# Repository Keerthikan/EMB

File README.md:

# EMB
Github for Embedded course

Lektion01: BlinkyLED

1. Assignment: FSM 
2. Assignment: Sliding thing.. Color detector... yeah you know!..

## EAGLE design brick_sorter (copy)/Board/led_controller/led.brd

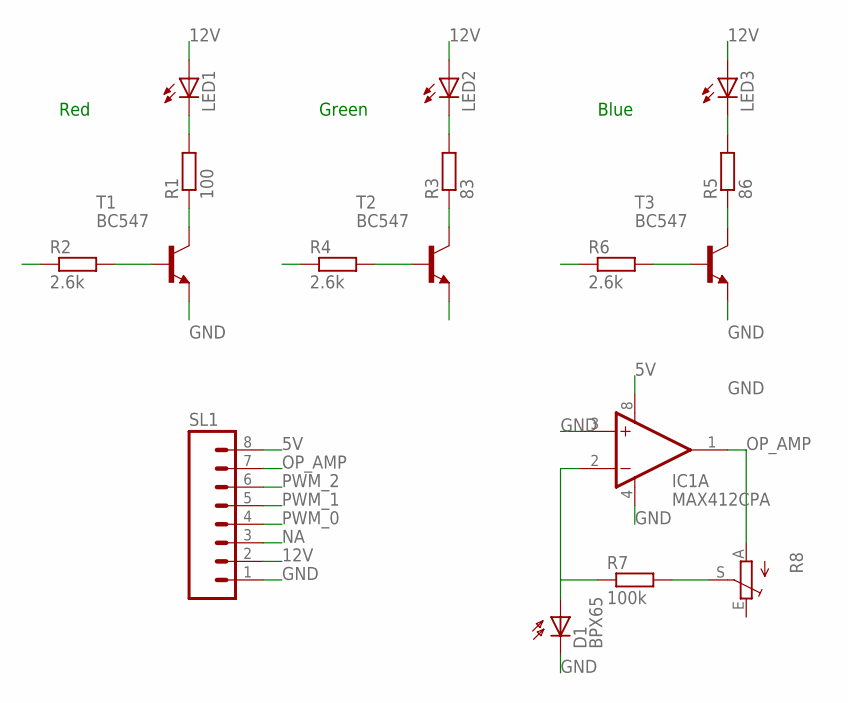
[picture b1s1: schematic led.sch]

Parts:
D1: BPX65
IC1: MAX412CPA; DIL08
LED1, LED2, LED3: LED_ELD260; LED_LD260
R1: 100; 0204/7
R2, R4, R6: 2.6k; 0204/7
R3: 83; 0204/7
R5: 86; 0204/7
R7: 100k; 0204/7
R8: TRIM_EU-B90P; SP19L
SL1: M08; 08P
T1, T2, T3: BC547; TO92

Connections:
5V: IC1.8 (V+), SL1.8
12V: LED1.A, LED2.A, LED3.A, SL1.2
GND: D1.K (C), IC1.3 (+IN), IC1.4 (V-), SL1.1, T1.1 (E), T2.1 (E), T3.1 (E)
unnamed: R4.2, T2.2 (B)
unnamed: LED1.K (C), R1.2
unnamed: R2.2, T1.2 (B)
unnamed: R1.1, T1.3 (C)
unnamed: LED2.K (C), R3.2
unnamed: R3.1, T2.3 (C)
unnamed: R6.2, T3.2 (B)
unnamed: LED3.K (C), R5.2
unnamed: R5.1, T3.3 (C)
unnamed: D1.A, IC1.2 (-IN), R7.1
unnamed: R7.2, R8.S
NA: SL1.3
OP_AMP: IC1.1 (OUT), R8.A, SL1.7
PWM_0: R2.1, SL1.4
PWM_1: R4.1, SL1.5
PWM_2: R6.1, SL1.6

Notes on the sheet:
Red
Green
Blue

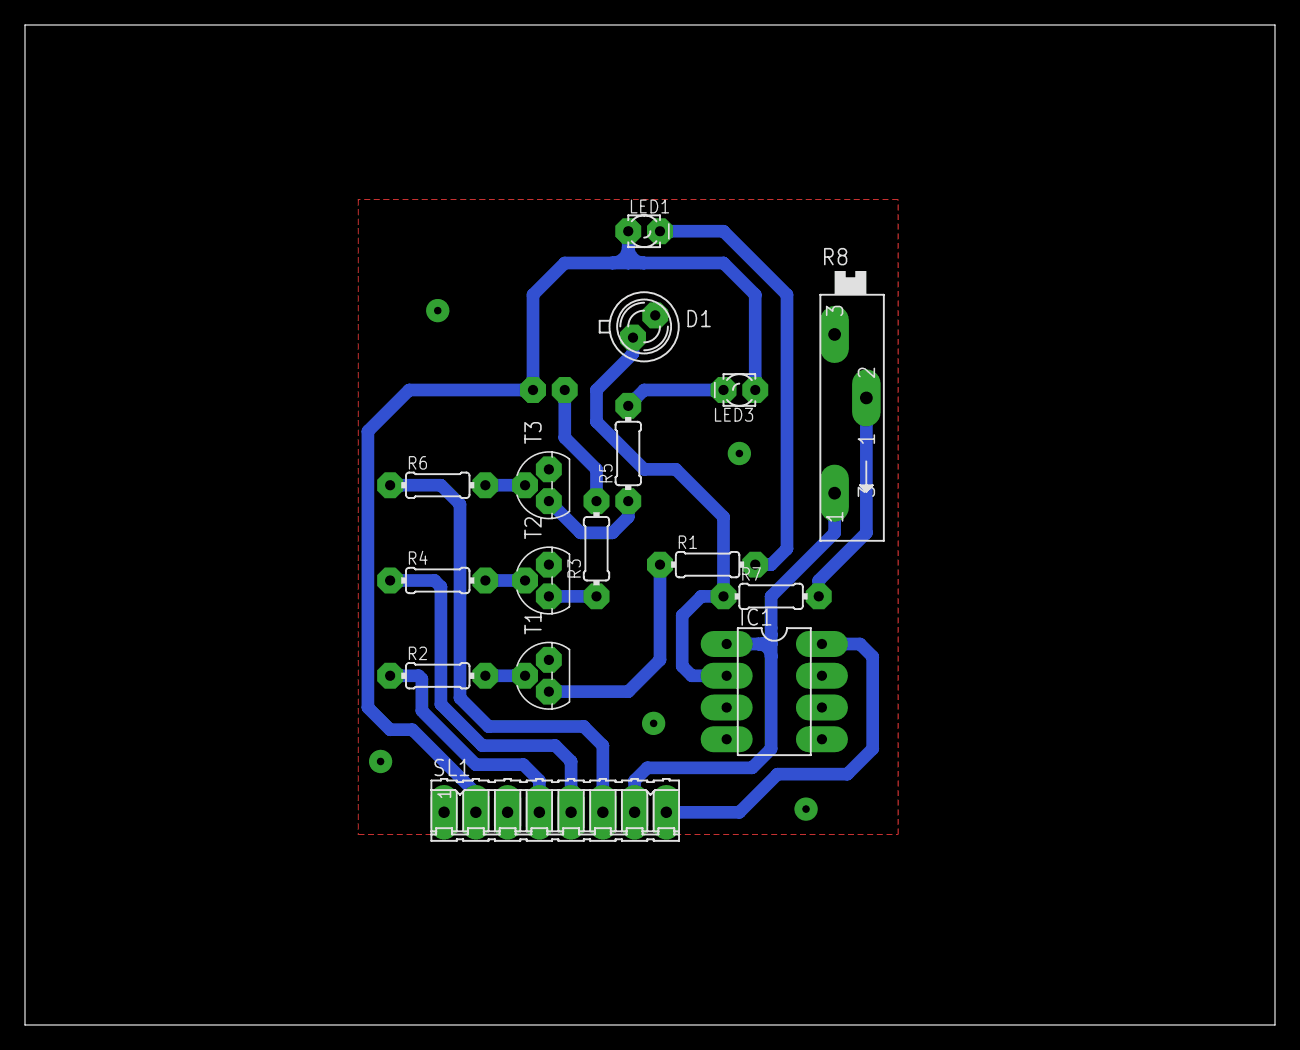
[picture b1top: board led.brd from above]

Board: 2 copper layers, 100.0 x 80.0 mm, 17 parts (1 on the bottom side), 18 nets.

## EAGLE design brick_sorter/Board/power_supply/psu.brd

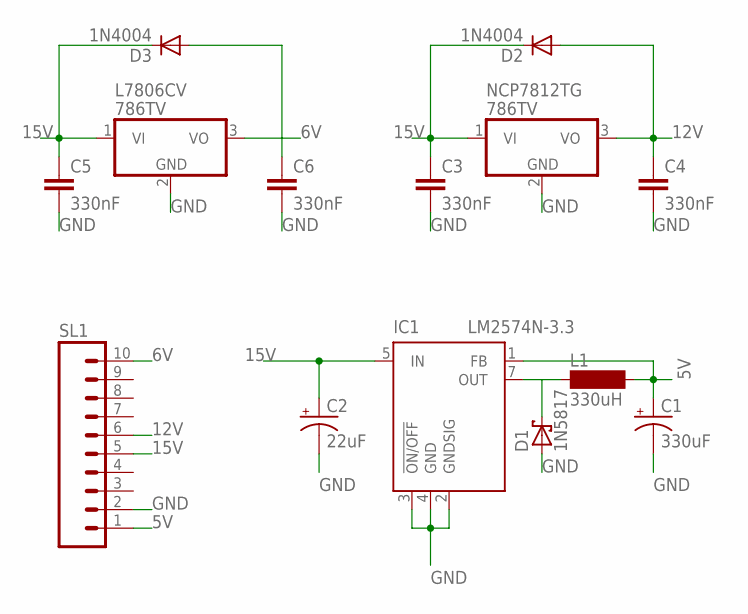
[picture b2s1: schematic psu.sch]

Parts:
C1: 330uF; E5-8,5
C2: 22uF; E5-5
C3, C4, C5, C6: 330nF; C050-030X075
D1: 1N5817; DO41-10
D2, D3: 1N4004; DO41-10
IC1: LM2574N-3.3; DIL08
L1: 330uH; BS11
L7806CV: 786TV; TO220V
NCP7812TG: 786TV; TO220V
SL1: M10; 10P

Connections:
5V: C1.+, IC1.1 (FB), L1.2, SL1.1
6V: C6.1, D3.A, L7806CV.3 (VO), SL1.10
12V: C4.1, D2.A, NCP7812TG.3 (VO), SL1.6
15V: C2.+, C3.1, C5.1, D2.C, D3.C, IC1.5 (IN), L7806CV.1 (VI), NCP7812TG.1 (VI), SL1.5
GND: C1.-, C2.-, C3.2, C4.2, C5.2, C6.2, D1.A, IC1.2 (GNDSIG), IC1.3 (!ON/OFF), IC1.4 (GND), L7806CV.2 (GND), NCP7812TG.2 (GND), SL1.2
LM_OUT: D1.C, IC1.7 (OUT), L1.1

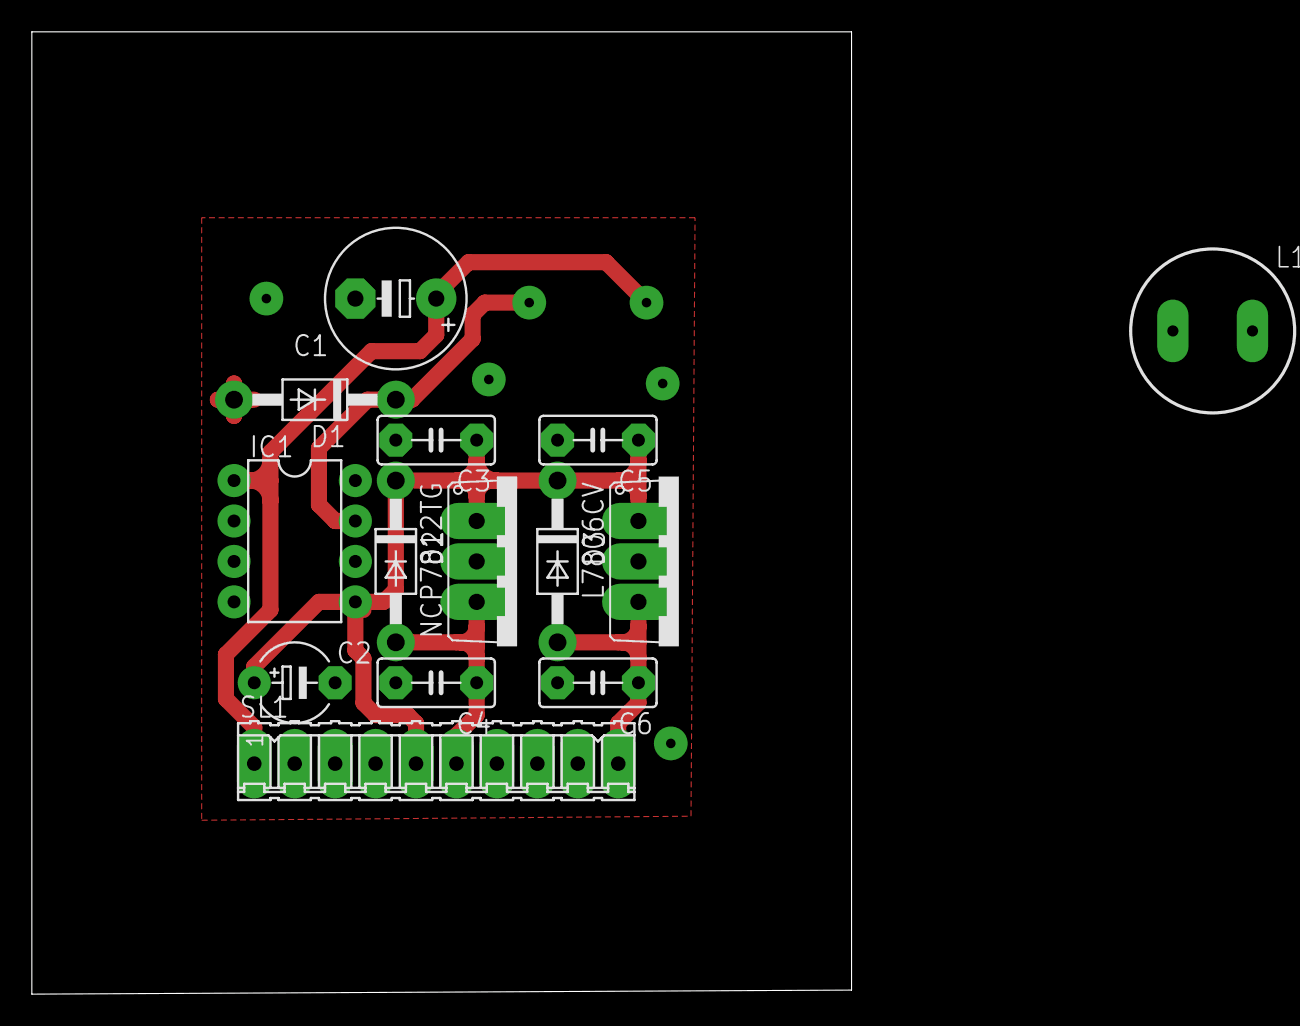
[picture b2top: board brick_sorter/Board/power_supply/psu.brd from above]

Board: 2 copper layers, 51.5 x 60.4 mm, 14 parts (0 on the bottom side), 6 nets.

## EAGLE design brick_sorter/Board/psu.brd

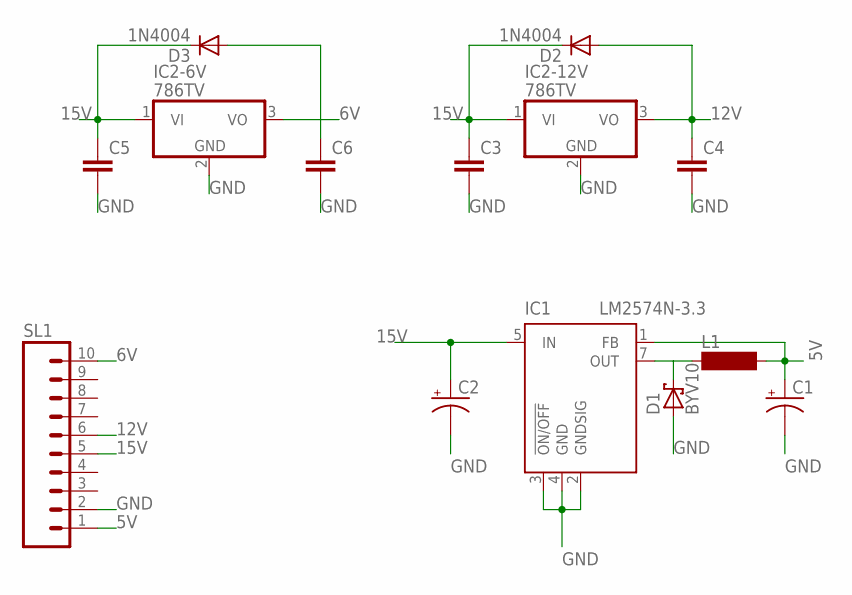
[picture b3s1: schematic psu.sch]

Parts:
C1: CPOL-USE5-8.5; E5-8,5
C2: CPOL-USE5-5; E5-5
C3, C4, C5, C6: C-EU050-030X075; C050-030X075
D1: BYV10; DO41-10
D2, D3: 1N4004; DO41-10
IC1: LM2574N-3.3; DIL08
IC2-6V, IC2-12V: 786TV; TO220V
L1: BS11
SL1: M10; 10P

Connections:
5V: C1.+, IC1.1 (FB), L1.2, SL1.1
6V: C6.1, D3.A, IC2-6V.3 (VO), SL1.10
12V: C4.1, D2.A, IC2-12V.3 (VO), SL1.6
15V: C2.+, C3.1, C5.1, D2.C, D3.C, IC1.5 (IN), IC2-6V.1 (VI), IC2-12V.1 (VI), SL1.5
GND: C1.-, C2.-, C3.2, C4.2, C5.2, C6.2, D1.A, IC1.2 (GNDSIG), IC1.3 (!ON/OFF), IC1.4 (GND), IC2-6V.2 (GND), IC2-12V.2 (GND), SL1.2
LM_OUT: D1.C, IC1.7 (OUT), L1.1

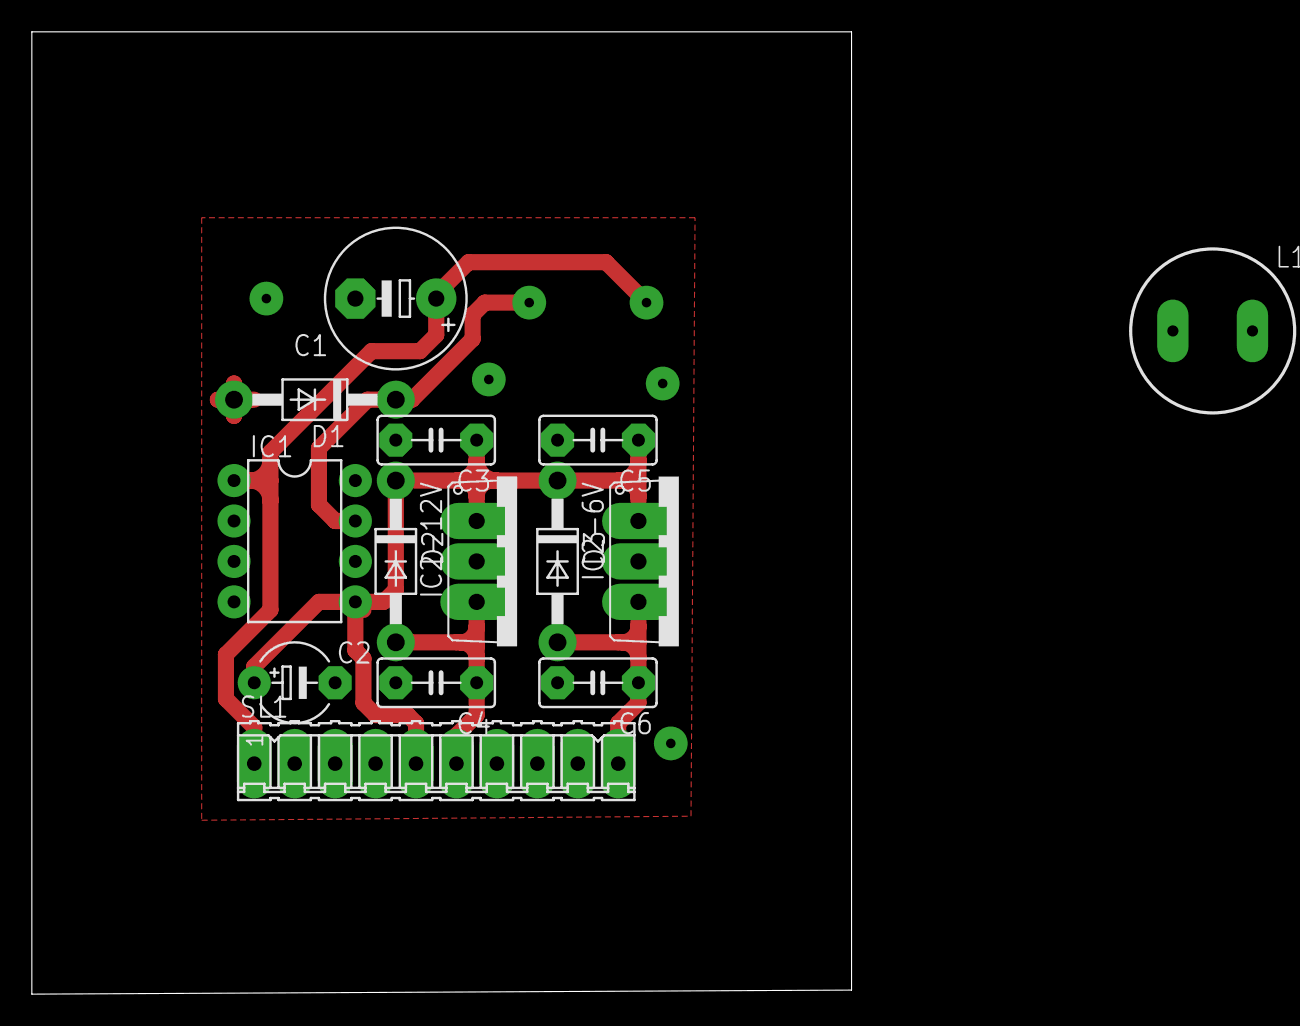
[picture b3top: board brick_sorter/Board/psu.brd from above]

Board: 2 copper layers, 51.5 x 60.4 mm, 14 parts (0 on the bottom side), 6 nets.

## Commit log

2015-09-11 First commit, FSM and blinkyled
2015-09-11 Hej kiddi
2015-09-12 VHDL finished fsm
2015-09-12 fsm_working
2015-09-12 removed project_2
2015-09-12 Components working, head broken
2015-09-12 Changed sensitivity list in fsm
2015-09-12 something
2015-09-15 added prototype of statemachine
2015-09-15 statemachina.xml
    Hvis der skal tilføjes nogle ændringer kan denne .xml fil bruges til at ændre statemachinen med i draw.io => det er en hjemmeside som hedder det.
2015-09-24 Updated statemachine
2015-09-24 Updated statemachine, again
2015-09-24 Hardware Diagrams
2015-09-24 Hardware diagrams, now PNG!
2015-09-24 resized hardware diagrams
2015-09-24 thomas
2015-09-24 sidste updates
2015-10-03 Rengøring!
2015-10-03 Bam!
2015-10-08 added right
2015-10-08 Board added
2015-10-08 Board v2.0
2015-10-08 Board v2.1 - now reversed
2015-10-11 Added second
2015-10-22 added boards
2015-10-22 Fixed planAhead (måske7)
2015-10-22 Nyt PDF board ting
2015-10-24 New board
2015-10-26 new ADC
2015-10-27 modfiied timing in ADC, waist time half newClock
2015-10-27 added led driver
2015-10-28 Added report and serial console
2015-10-29 kiddi init report part
2015-10-29 Updates to report
2015-10-29 Added kiddi report to report
2015-10-30 rettelse til aDC, blackbox problems
2015-10-30 efficiency diagram
2015-10-30 head added
2015-10-30 updated ucf
2015-10-30 added
2015-10-30 idioti push
2015-10-30 Fy for satan
2015-10-30 added seri_term
2015-10-30 last commit
2015-10-30 Working LED shifting
2015-10-30 added some files
2015-10-30 head working
2015-10-31 report updates
2015-10-31 kiddi report without Images
2015-10-31 led_report
2015-10-31 ændret at LED_on tænder og slukker ikke
2015-11-01 billeder
2015-11-01 new MAin
2015-11-01 statemachine led_driver
2015-11-01 ADC tikz added
2015-11-01 tikz control
2015-11-01 led driver fix
2015-11-01 Værsågod!
2015-11-01 my thign
2015-11-01 entitty missing
2015-11-01 ent_control
2015-11-01 fullSystem.tex added
2015-11-01 report, going for the home stretch
2015-11-01 report final?
2015-11-01 +images
2015-11-01 Mere very short introduction
2015-11-01 new statemachine
2015-11-01 mere commit
2015-11-01 Final Report!
2015-11-01 final_brickSorrter/
2015-11-01 More Final report
2015-11-01 deleted brick_sorter copy
2015-11-05 Init project 2
2015-11-05 moved file
2015-11-05 folder
2015-11-05 new init model
2015-11-05 Here we go!
2015-11-05 added project description
2015-12-18 and so it begins
2015-12-19 Another one for the repo!
2015-12-19 Some changes are in order!
2015-12-19 Couldn't add it via MAC
2015-12-19 Continue!
2015-12-19 Continue this!
2015-12-19 or this
2015-12-20 a commit
2015-12-20 pov.tex ...
2015-12-20 another commit
2015-12-20 main merge
2015-12-20 Display controller
2015-12-20 added a stop
2015-12-20 Have a hashtag! #
2015-12-20 memory.tex
2015-12-21 rettelse
2015-12-21 rettelser
2015-12-21 A commit!
2015-12-21 Final commit?
